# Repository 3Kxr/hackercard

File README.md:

# hackercard
> A personal business card designed based on NFC card technology

### BOM
- U1    NT3H2111W0FHKH
- LED KT-0805Y
- 47Ω resistor 0603WAF470JT5E
- 220nF capacitor CL10B224KA8NNNC

### PCB

### 3D

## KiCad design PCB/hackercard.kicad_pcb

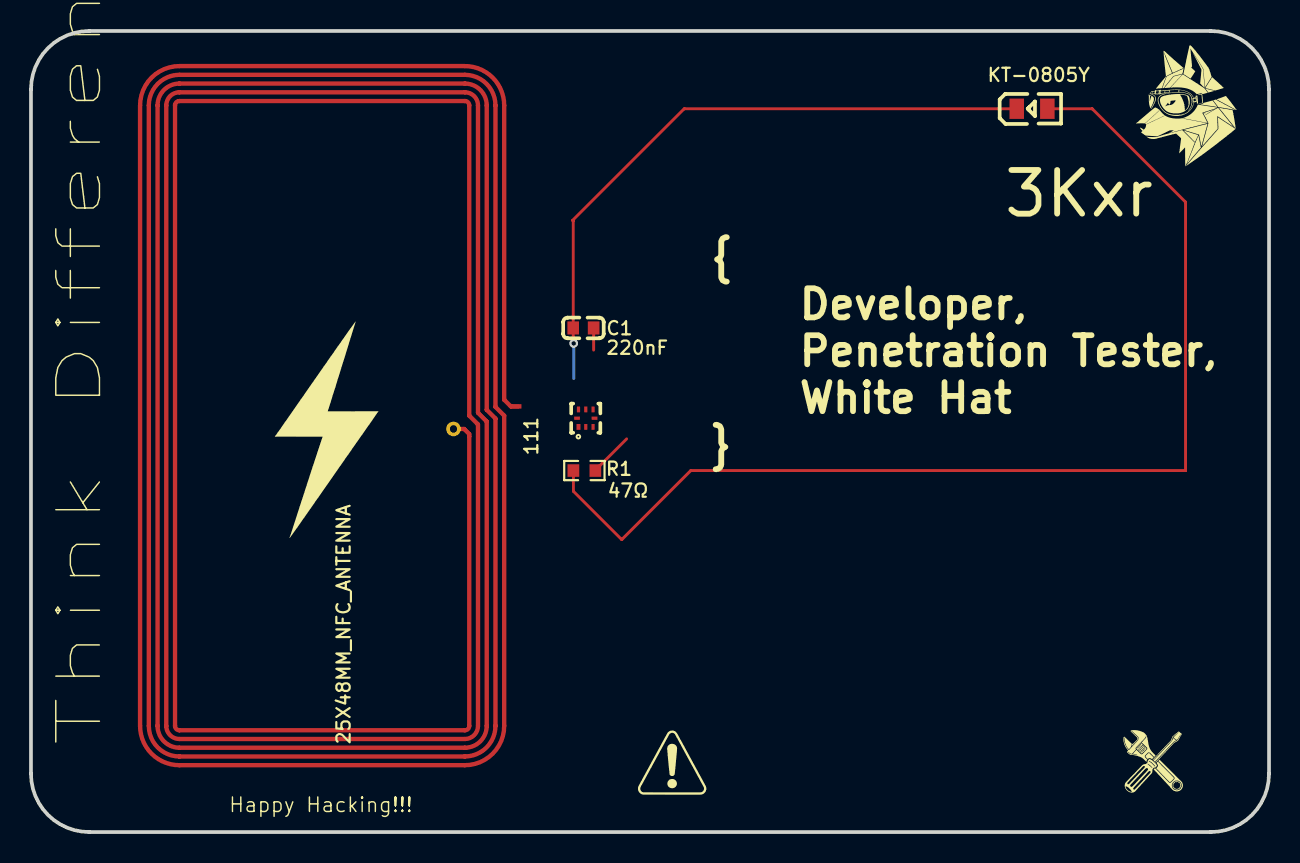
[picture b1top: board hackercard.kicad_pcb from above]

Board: 2 copper layers, 85.0 x 55.0 mm, 5 parts (0 on the bottom side), 5 nets.

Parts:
111: 25X48MM_NFC_ANTENNA
C1: 220nF; C0603
LED1: KT-0805Y; LED0805-R-RD
R1: 47Ω; R0603
U1: NT3H2111W0FHKH; XQFN-8_L1.6-W1.6-P0.50-BL_NT3H2111W0FHKH

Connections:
unnamed: LED1.1 (+), R1.1
unnamed: C1.1, LED1.2 (-), U1.2 (VSS)
unnamed: 111.P$2, U1.1 (LA)
unnamed: 111.P$1, U1.8 (LB)
unnamed: C1.2, R1.2, U1.6 (VCC), U1.7 (VOUT)

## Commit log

2026-03-22 add .gitignore
2026-03-22 commit item
